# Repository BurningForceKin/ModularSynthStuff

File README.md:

# ModularSynthStuff
Mostly Eurorack modules. Mostly designed by me.
These PCBs are made in Kicad.
You can use the zipped Gerber files to order these PCBs from a manufacturer (I use JLCPCB). Be aware that you need to order more than one copy of a PCB.
If you have a 3D printer, you can save a few bucks by printing the panels. Just download the STL files.

There is still a lot of things to do, like ordering my own PCBs to test them (Yes, I still don't know if all the modules will work.).

[You can now visit the shop!!!](https://www.tindie.com/stores/tswts/)

# [DIY Case](https://github.com/BurningForceKin/ModularSynthStuff/tree/gh-pages/DIYcase)
Plans for a case with 50cm rails. I'm planning to build this sometime out of OSB plates. The back of the case has a big "SYNTHESIZER" print, so that normal people know wtf it is.

# [Doei](https://github.com/BurningForceKin/ModularSynthStuff/tree/gh-pages/HeadphoneOutV1)
Doei is a headphone amp, based on the CMoy schematic. V1 ready to go! Now including a zine!

V1 Test notes: Use UNSHROUDED header for power. A100K pot works, but A200K might be even better.

# [PACO!](https://github.com/BurningForceKin/ModularSynthStuff/tree/gh-pages/Paco)
PACO! is a simple routing module, double signal splitter or bypasser. It's just a bunch of jacks connected to a toggle switch.

V1 Test Notes: Use a SPDT switch with round legs. The common ones with rectangular legs won't fit right. V2 will have a better footprint for the switch.

Ready to go! Features a zine to print out.

# [Tuner](https://github.com/BurningForceKin/ModularSynthStuff/tree/gh-pages/Tuner)
Handy for keeping your synth in tune during gigs. It's a Eurorack recreation of LMNC's tuner schematic, as seen in his VCO module. This one also features a zine!

Link: https://www.lookmumnocomputer.com/projects#/1222-performance-vco

This module isn't supposed to be super accurate, so don't trust it too much. I just use it to make sure my oscillator is set to the right frequency. (It sounds like an A when I hit the A on my keyboard)

The module is 5HP wide. It only takes power from the +12V rail and converts it to 5V.

V1 Test Notes: Use UNSHROUDED header for power. IT WORKS!! LEDs are a bit bright, so I might increase the resistor values.

V2 Notes: Printing error at the powerheader :/

Copyright notes: This module is obviously ripped from LMNC's VCO (which is copied from someone elses tuner). I'm not selling this design, untill I have premission.

# Braids
I added some files for people who want to make a Through-hole Braids. You can download a PDF of my building instructions and a 3D file of the front panel.

# [Distortion](https://github.com/BurningForceKin/ModularSynthStuff/tree/gh-pages/Distortion)

A straight-forward distortion module to bring a bit more character to your boring oscillators. The circuit is based on Niklas Ronnberg's distortion. My version removes the hardclipping (now it only does softclipping) and adds a bypass switch.

Link: http://familjenronnberg.se/~niklas/diy/eurorack/dist/

The module is 5HP wide. A TL072 should work as well.
You can also choose to download the PCB version of the panel.

V1 Test notes: The pot is reversed :( It hase the same SPDT footprint as PACO!, so make sure you use a switch with round legs. Alternatively, you can connect the lower two pins on the switch's footprint, so it's always on. That way can ditch the switch altogether. Also, the position of the switch makes it look a little weird...
V2 Notes: All bugs are fixed, everything works! I'm using blue clipping LEDs, but red ones are probably better.

# [Wesp](https://github.com/BurningForceKin/ModularSynthStuff/tree/gh-pages/Wesp)

A Wasp-type filter. I based it on Jurgen Haibles'schematic, so all the credit should to him. This version uses a LM13700 instead of two CA3080s. The only options to get your hands on a Wasp filter nowadays is to get the Doepfer filter or the Berhinger Wasp Deluxe. If you want to DIY it you can get the Random Source dual filter or Forestcaver's SMD PCB (or maybe something else). All of which are great filters! Unfortunately I'm a stubborn idiot, so I tried designing my own version.
This is the first dubble-PCB design. It only needs the +12V line to make +5V. Not sure if the PSU will like this, though.

Link: http://modular.fonik.de/pdf/Wasp%20Filter%20clone.pdf

V1 Test notes: IT WORKS DUDE! There are a few things to update. Add a voltageclamp and diode on the CV input. Add attenuator? Cuttoff is logaritmic. Discard or fix distortion (make it louder plz). 5V regulator footprint is the wrong way around.
The resonance is the right way around, i think. Also, Schmitt-triggers make it go nuts.

Copyright note: Jurgen's new site states that all his designs are for educational purposes only, and I want to respect that. So, I won't be selling this module in the future, unless I turn it into a truely unique thing.
V2 removed the distortion and added CV-attenuation. To make it even more original, V3 should have a boosted distortion, only LP/HP/BP, CV-att, and self-oscillation.

# [Omnitool](https://github.com/BurningForceKin/ModularSynthStuff/tree/gh-pages/Omnitool)
A utility module inspired by the MS-20. It features a glide, S&H and manual button. The button is normalled to the S&H clock-input. It also has a negative output, which should act as an S-Trig.

The module uses little parts, so the build will be really easy. The only part that is tricky to find is the LF398 IC. Luckily, I found one on Aliexpress. The button can be any single-pole momentary switch, as long as it fits the panel. I will design the panel for a Cherry switch.

V1 Notes: The glide works, but is a bit twitchy. (Make the cap smaller?) The button only works on the 0>5V side, but with a noticable delay when combined with a Doepfer EG. The LED is routed wrong :( The LF398 is yet to be tested. Als, the transistor/powerconverter footprints are wrong. And the Cherry switch needs to fit better.
A total failure? Yes, but also no.

# [Printable Panels](https://github.com/BurningForceKin/ModularSynthStuff/tree/gh-pages/printablepanels)
These are the panels I designed for the DIY modules in my system. It saves me some money (I think ±60,-) when buying PCB-sets. It also allows me to make my system look a little more visually consistent. In comparison to metal faceplates they're kinda flimsy, but the PCB on the back makes up for it. Feel free to download and print them for yr rack.

Folder includes panels for:
<ul>
  <li> Kassutronics KS-20 VCF </li>
  <li> Kassutronics CEM3340 VCO</li>
  <li> Kassutronics ASR</li>
  <li> Frequency Central More VCAs</li>
  <li> Frequency Central Raging Bull VCF</li>
  <li> Frequency Central MethAmp Distortion</li>
  <li> Blank panel with poem by Nael</li>
  <li> Erica Synths MIDI to CV</li>
  <li> David Haillant's Simple VCO</li>
 </ul>

# [Marble Hornet](https://github.com/BurningForceKin/ModularSynthStuff/tree/gh-pages/marblehornet)
I was messing with the Wasp filter to make it more unique until I found a few mods that worked. I renamed this version of the Wesp to Marble Hornet.
This folder has a version in the Kosmo format. I'm not planning on ordering these big PCBs, so don't expect a revision. That said, I fixed all the bugs (lol) from the V1 Wesp, so it should work first try.

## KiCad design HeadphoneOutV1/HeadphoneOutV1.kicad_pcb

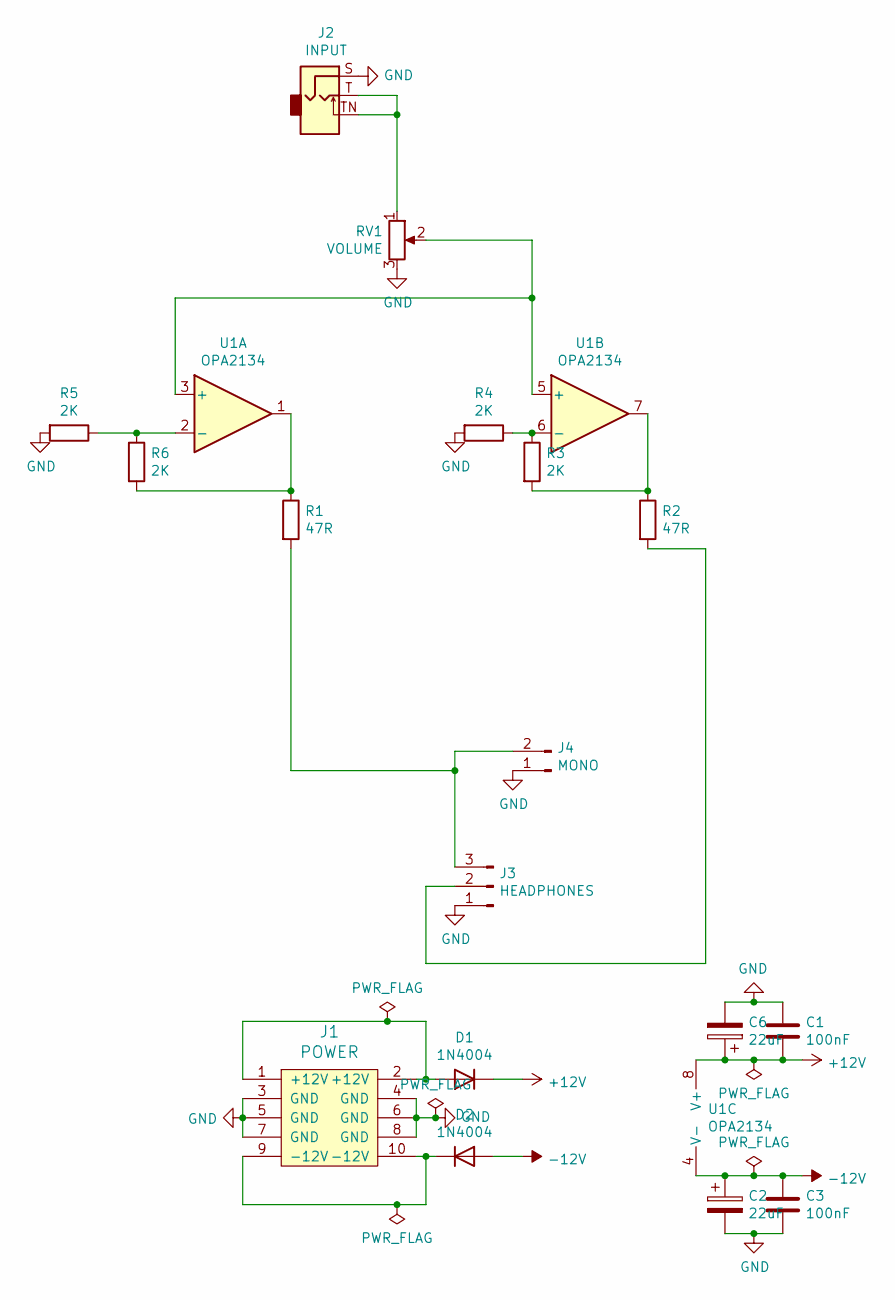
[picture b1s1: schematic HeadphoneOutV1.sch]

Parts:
C1, C3: 100nF; C_Disc_D4.3mm_W1.9mm_P5.00mm
C2, C6: 22uF; CP_Radial_D5.0mm_P2.50mm
D1, D2: 1N4004; D_DO-41_SOD81_P10.16mm_Horizontal
J1: POWER; PinSocket_2x05_P2.54mm_Vertical
J2: INPUT; Jack_3.5mm_QingPu_WQP-PJ398SM_Vertical_CircularHoles
J3: HEADPHONES; PinSocket_1x03_P2.54mm_Vertical
J4: MONO; PinSocket_1x02_P2.54mm_Vertical
R1, R2: 47R; R_Axial_DIN0204_L3.6mm_D1.6mm_P5.08mm_Horizontal
R3, R4, R5, R6: 2K; R_Axial_DIN0204_L3.6mm_D1.6mm_P5.08mm_Horizontal
RV1: VOLUME; 9MM_SNAP-IN_POT
U1: OPA2134; DIP-8_W7.62mm_Socket

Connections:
+12V: C1.2, C6.1, D1.1 (K), U1.8 (V+)
-12V: C2.1, C3.1, D2.2 (A), U1.4 (V-)
GND: C1.1, C2.2, C3.2, C6.2, J1.3 (GND), J1.4 (GND), J1.5 (GND), J1.6 (GND), J1.7 (GND), J1.8 (GND), J2.S, J3.1, J4.1, R4.2, R5.2, RV1.3
unnamed: D1.2 (A), J1.1 (+12V), J1.2 (+12V)
unnamed: D2.1 (K), J1.9 (-12V), J1.10 (-12V)
unnamed: J2.T, J2.TN, RV1.1
unnamed: J3.2, R2.2
unnamed: J3.3, J4.2, R1.2
unnamed: R1.1, R6.2, U1.1
unnamed: R2.1, R3.2, U1.7
unnamed: R3.1, R4.1, U1.6 (-)
unnamed: R5.1, R6.1, U1.2 (-)
unnamed: RV1.2, U1.3 (+), U1.5 (+)

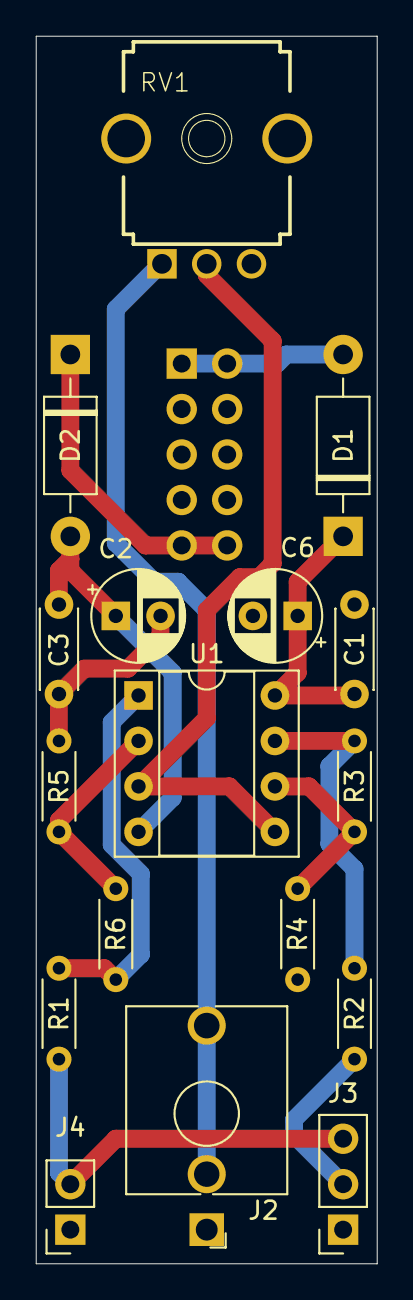
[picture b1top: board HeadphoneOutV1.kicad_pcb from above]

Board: 2 copper layers, 19.1 x 68.6 mm, 18 parts (1 on the bottom side), 13 nets.

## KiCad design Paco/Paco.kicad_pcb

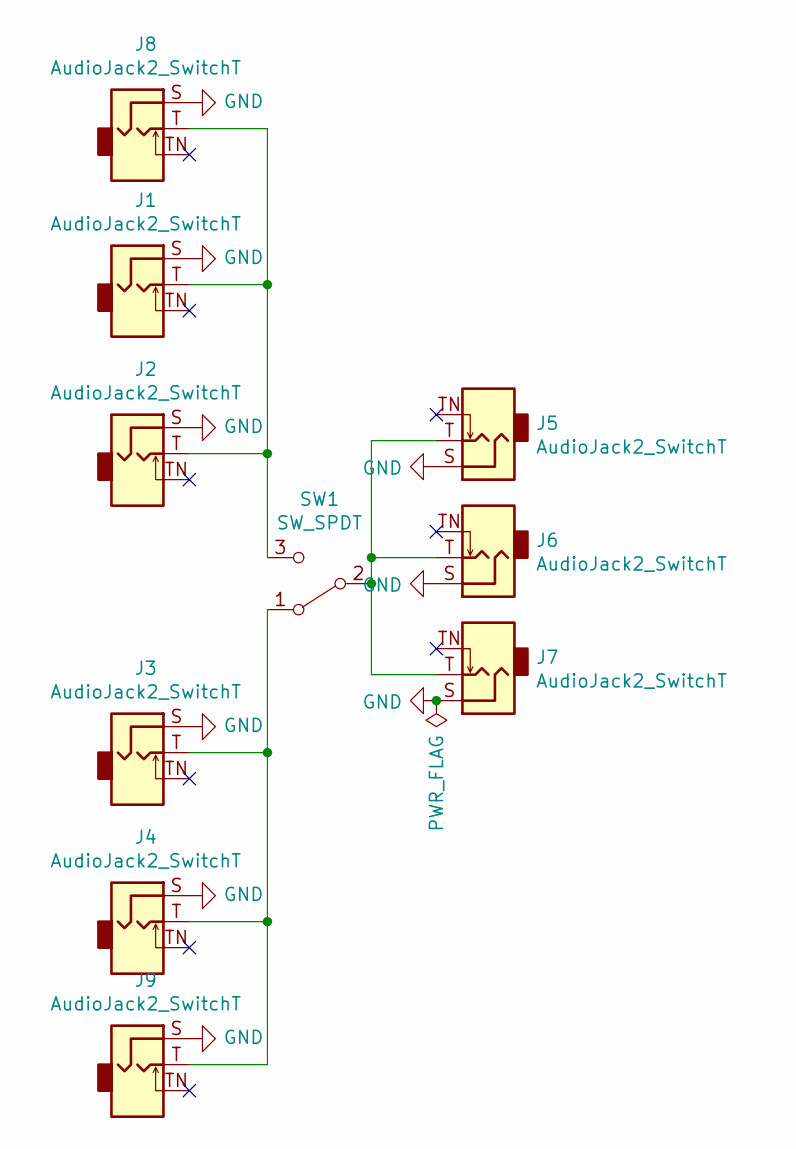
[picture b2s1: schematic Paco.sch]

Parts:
J1, J2, J3, J4, J5, J6, J7, J8, J9: AudioJack2_SwitchT; Jack_3.5mm_QingPu_WQP-PJ398SM_Vertical_CircularHoles
SW1: SW_SPDT; Toggle_Switch_100SP1T1B4M2QE

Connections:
GND: J1.S, J2.S, J3.S, J4.S, J5.S, J6.S, J7.S, J8.S, J9.S
unnamed: J1.T, J2.T, J8.T, SW1.3 (C)
unnamed: J3.T, J4.T, J9.T, SW1.1 (A)
unnamed: J5.T, J6.T, J7.T, SW1.2 (B)

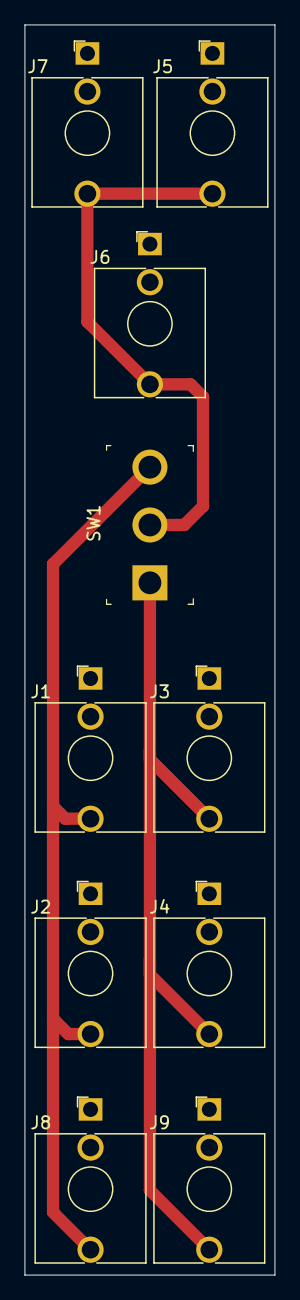
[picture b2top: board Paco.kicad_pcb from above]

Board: 2 copper layers, 20.3 x 101.6 mm, 10 parts (0 on the bottom side), 4 nets.

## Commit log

2021-01-05 Set theme jekyll-theme-minimal
2021-01-28 Rename index.md to hulp.md
2021-01-28 Rename index.md to docs/index.md
